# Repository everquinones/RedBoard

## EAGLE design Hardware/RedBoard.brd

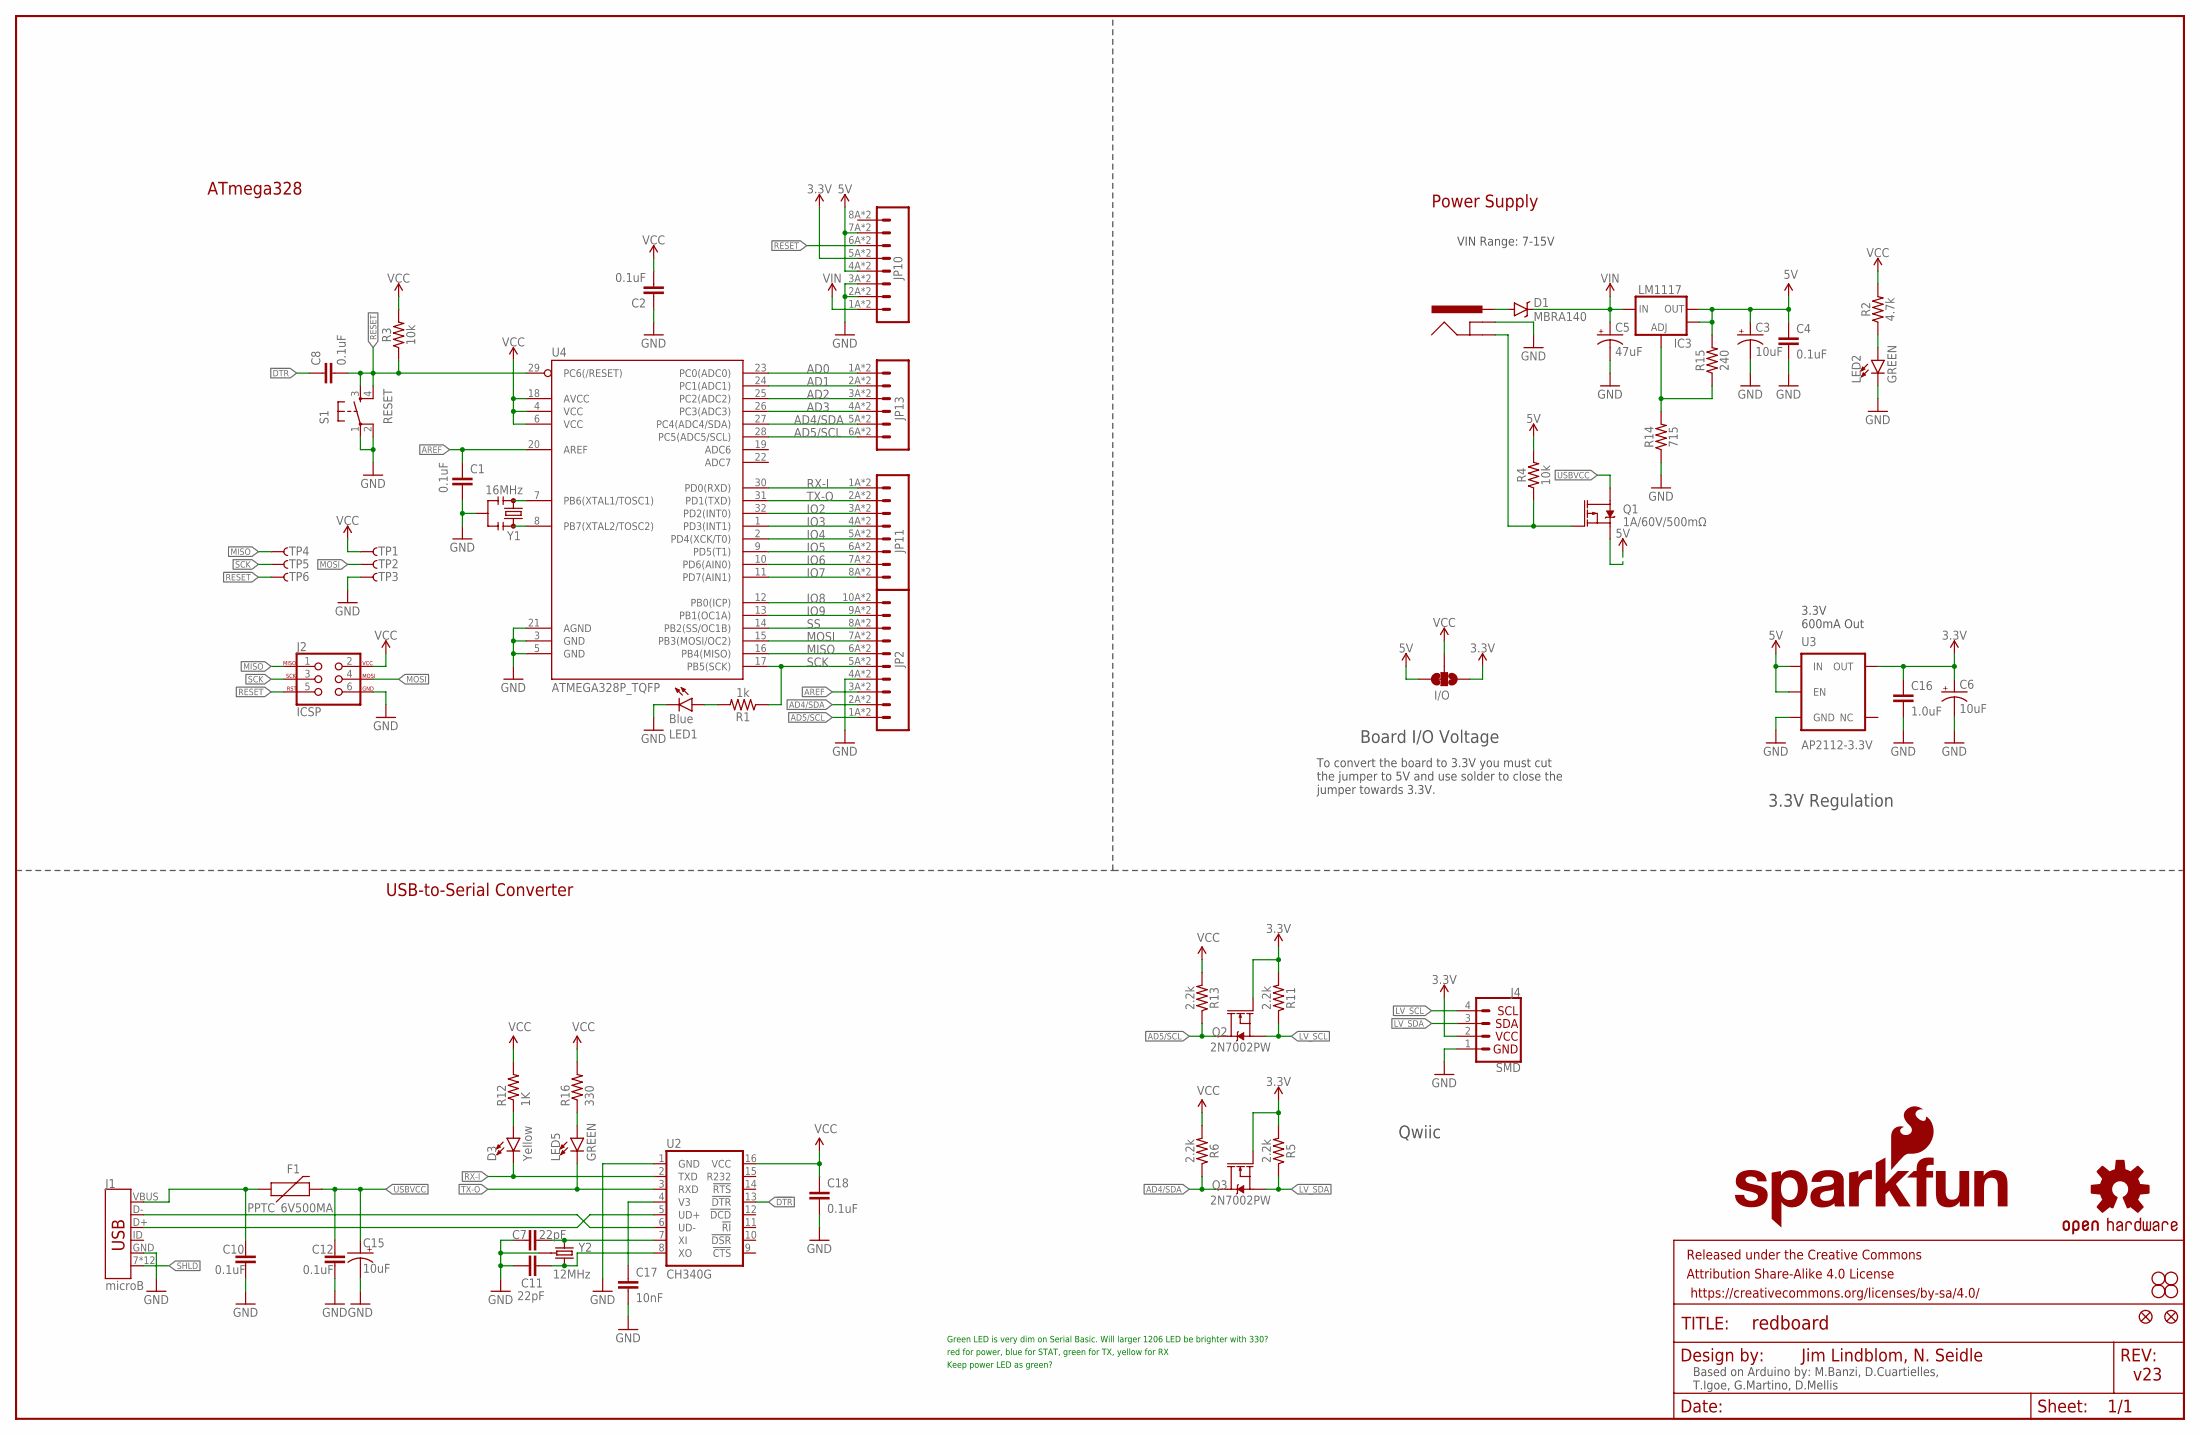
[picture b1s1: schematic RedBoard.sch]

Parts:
C1, C2, C4, C8, C10, C12: 0.1uF; 0603
C3, C6, C15: 10uF; EIA3216
C5: 47uF; PANASONIC_D
C7, C11: 22pF; 0603
C16: 1.0uF; 0603-CAP
C17: 10nF; 0603-CAP
C18: 0.1uF; 0603-CAP
D1: MBRA140; SMA-DIODE
D3: Yellow; LED-1206-HIDDENSILK
F1: PPTC_6V500MA; 0805
FRAME1: FRAME-LEDGER; CREATIVE_COMMONS
I/O: JUMPER-SMT_3_1-NC_TRACE_SILK; SMT-JUMPER_3_1-NC_TRACE_SILK
IC3: LM1117; SOT223-ALT1
J1: microB; USB-MICROB-PTH
J2: ICSP; 2X3_SMT_POSTS
J3: POWER_JACKSUPER_BOMB_DIGITY; POWER_JACK_SMD_OVERPASTE_SUPER_BOMB_DIGITY
J4: SMD; 1X04_1MM_RA
JP1: SFE_LOGO_NAME.1_INCH; SFE_LOGO_NAME_.1
JP2: M10SMD_COMBO; 1X10_SMD_COMBINED
JP3, JP4, JP5, JP6: STAND-OFF
JP7: SFE_LOGO_FLAME.1_INCH; SFE_LOGO_FLAME_.1
JP8, JP9: FIDUCIAL1X2; FIDUCIAL-1X2
JP10: M08SMD-COMBO; 1X08_SMD_COMBINED
JP11: JP11; 1X08_SMD_COMBINED
JP13: M06SMD-STRAIGHT-COMBO; 1X06_SMD_STRAIGHT_COMBO
LED1: Blue; LED-1206-HIDDENSILK
LED2, LED5: GREEN; LED-1206-HIDDENSILK
Q1: 1A/60V/500mΩ; SOT23-3
Q2, Q3: 2N7002PW; SOT323
R1: 1k; 0603
R2: 4.7k; 0603
R3, R4: 10k; 0603
R5, R6, R11, R13: 2.2k; 0603
R12: 1K; 0603-RES
R14: 715; 0603
R15: 240; 0603
R16: 330; 0603-RES
S1: RESET; TACTILE-SWITCH-SMD
TP1, TP2, TP3, TP4, TP5, TP6: TP-3x5; PAD.03X.05
U2: CH340G; SO016
U3: AP2112-3.3V; SOT23-5
U4: ATMEGA328P_TQFP; TQFP32-08
U$16: OSHW-LOGOS; OSHW-LOGO-S
Y1: 16MHz; RESONATOR-SMD-3.2X1.3
Y2: 12MHz; CRYSTAL-SMD-3.2X2.5

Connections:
3.3V: C6.+, C16.1, I/O.1, J4.2 (VCC), JP10.5A (5), JP10.5B (5), Q2.1 (G), Q3.1 (G), R5.2, R11.2, U3.5 (OUT)
5V: C3.+, C4.1, I/O.3, IC3.2 (OUT), IC3.4 (OUT), JP10.4A (4), JP10.4B (4), JP10.7A (7), JP10.7B (7), Q1.2 (S), R4.2, R15.2, U3.1 (IN), U3.3 (EN)
!DTR: C8.1, U2.13 (!DTR)
AD0: JP13.1A (1), JP13.1B (1), U4.23 (PC0(ADC0))
AD1: JP13.2A (2), JP13.2B (2), U4.24 (PC1(ADC1))
AD2: JP13.3A (3), JP13.3B (3), U4.25 (PC2(ADC2))
AD3: JP13.4A (4), JP13.4B (4), U4.26 (PC3(ADC3))
AD4/SDA: JP2.2A (2), JP2.2B (2), JP13.5A (5), JP13.5B (5), Q3.3 (D), R6.1, U4.27 (PC4(ADC4/SDA))
AD5/SCL: JP2.1A (1), JP2.1B (1), JP13.6A (6), JP13.6B (6), Q2.3 (D), R13.1, U4.28 (PC5(ADC5/SCL))
AREF: C1.1, JP2.3A (3), JP2.3B (3), U4.20 (AREF)
GND: C1.2, C2.1, C3.-, C4.2, C5.-, C6.-, C7.1, C10.2, C11.1, C12.2, C15.-, C16.2, C17.2, C18.2, J1.GND, J2.6, J3.GND (GNDBREAK), J4.1 (GND), JP2.4A (4), JP2.4B (4), JP10.2A (2), JP10.2B (2), JP10.3A (3), JP10.3B (3), LED1.C, LED2.C, R14.1, S1.1, S1.2, TP3.P$1, U2.1 (GND), U3.2 (GND), U4.3 (GND), U4.5 (GND), U4.21 (AGND), Y1.2, Y2.2 (GND), Y2.4 (GND)
INSERT: J3.P$4 (GND), Q1.1 (G), R4.1
IO2: JP11.3A (3), JP11.3B (3), U4.32 (PD2(INT0))
IO3: JP11.4A (4), JP11.4B (4), U4.1 (PD3(INT1))
IO4: JP11.5A (5), JP11.5B (5), U4.2 (PD4(XCK/T0))
IO5: JP11.6A (6), JP11.6B (6), U4.9 (PD5(T1))
IO6: JP11.7A (7), JP11.7B (7), U4.10 (PD6(AIN0))
IO7: JP11.8A (8), JP11.8B (8), U4.11 (PD7(AIN1))
IO8: JP2.10A (10), JP2.10B (10), U4.12 (PB0(ICP))
IO9: JP2.9A (9), JP2.9B (9), U4.13 (PB1(OC1A))
LV_SCL: J4.4 (SCL), Q2.2 (S), R11.1
LV_SDA: J4.3 (SDA), Q3.2 (S), R5.1
MISO: J2.1, JP2.6A (6), JP2.6B (6), TP4.P$1, U4.16 (PB4(MISO))
MOSI: J2.4, JP2.7A (7), JP2.7B (7), TP2.P$1, U4.15 (PB3(MOSI/OC2))
unnamed: LED1.A, R1.2
unnamed: LED2.A, R2.1
unnamed: U4.7 (PB6(XTAL1/TOSC1)), Y1.1
unnamed: U4.8 (PB7(XTAL2/TOSC2)), Y1.3
unnamed: LED5.A, R16.1
unnamed: D3.A, R12.1
unnamed: C11.2, U2.8 (XO), Y2.3 (2)
unnamed: C7.2, U2.7 (XI), Y2.1
unnamed: J1.D-, U2.6 (UD-)
unnamed: J1.D+, U2.5 (UD+)
unnamed: IC3.1 (ADJ), R14.2, R15.1
PWRIN: D1.A, J3.VIN0 (PWR)
RESET: C8.2, J2.5, JP10.6A (6), JP10.6B (6), R3.1, S1.3, S1.4, TP6.P$1, U4.29 (PC6(/RESET))
RX-I: D3.C, JP11.1A (1), JP11.1B (1), U2.2 (TXD), U4.30 (PD0(RXD))
SCK: J2.3, JP2.5A (5), JP2.5B (5), R1.1, TP5.P$1, U4.17 (PB5(SCK))
SHLD: J1.7 (SHIELD), J1.SHEILD2 (SHIELD), J1.SHIELD, J1.SHIELD3 (SHIELD), J1.SHIELD4 (SHIELD), J1.SHIELD5 (SHIELD), J1.SHIELD6 (SHIELD), J1.SHIELD8 (SHIELD), J1.SHIELD9 (SHIELD), J1.SHIELD10 (SHIELD), J1.SHIELD11 (SHIELD), J1.SHIELD12 (SHIELD)
SS: JP2.8A (8), JP2.8B (8), U4.14 (PB2(SS/OC1B))
TX-O: JP11.2A (2), JP11.2B (2), LED5.C, U2.3 (RXD), U4.31 (PD1(TXD))
USBVCC: C12.1, C15.+, F1.2, Q1.3 (D)
V3: C17.1, U2.4 (V3)
VCC: C2.2, C18.1, I/O.2, J2.2, R2.2, R3.2, R6.2, R12.2, R13.2, R16.2, TP1.P$1, U2.16 (VCC), U4.4 (VCC), U4.6 (VCC), U4.18 (AVCC)
VIN: C5.+, D1.C, IC3.3 (IN), JP10.1A (1), JP10.1B (1)
VUSB: C10.1, F1.1, J1.VBUS

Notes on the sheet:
Power Supply
ATmega328
USB-to-Serial Converter
Based on Arduino by: M.Banzi, D.Cuartielles, T.Igoe, G.Martino, D.Mellis
Jim Lindblom, N. Seidle
v23
VIN Range: 7-15V
3.3V Regulation
3.3V 600mA Out
Green LED is very dim on Serial Basic. Will larger 1206 LED be brighter with 330?
Board I/O Voltage
To convert the board to 3.3V you must cut the jumper to 5V and use solder to close the jumper towards 3.3V.
Qwiic
red for power, blue for STAT, green for TX, yellow for RX
Keep power LED as green?

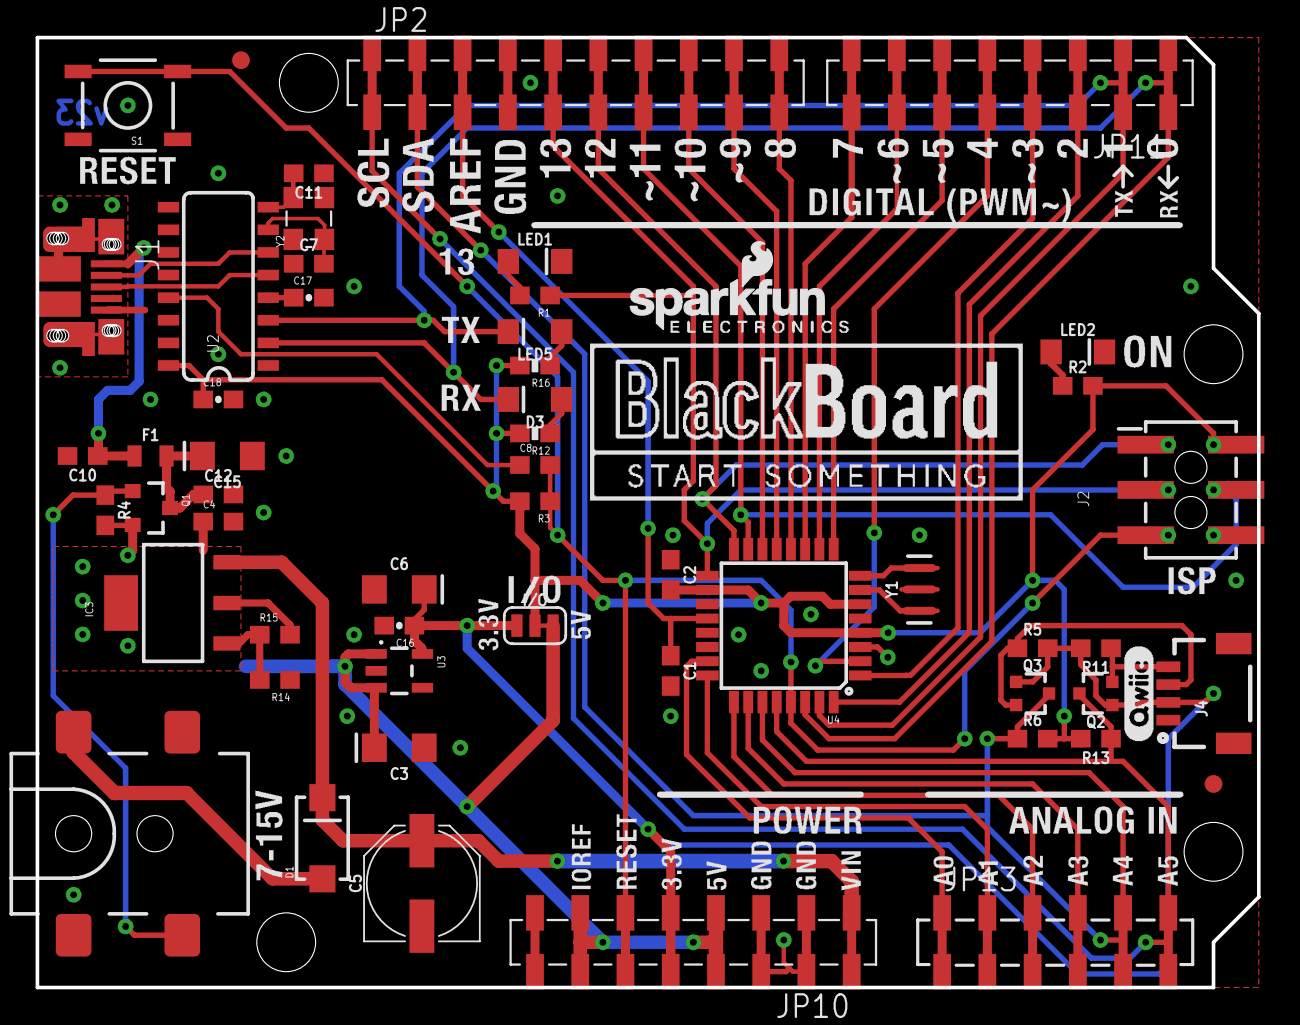
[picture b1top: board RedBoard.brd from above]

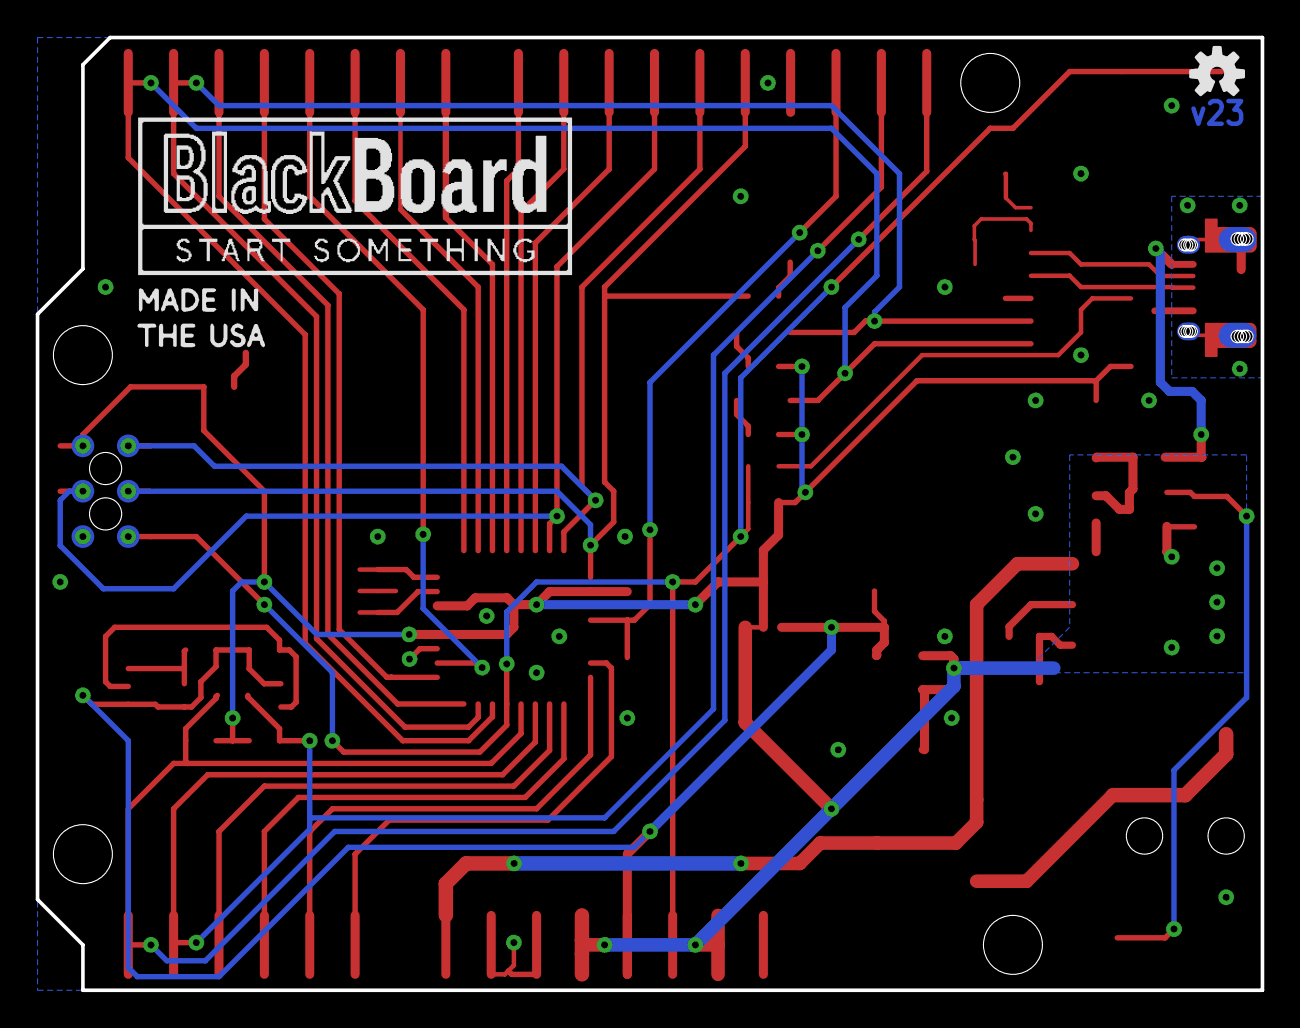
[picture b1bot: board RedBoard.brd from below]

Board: 2 copper layers, 68.6 x 53.3 mm, 72 parts (9 on the bottom side), 47 nets.

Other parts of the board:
U$1, U$3: BLACKBOARDLOGO#PNG
U$2: (QWIIC)
U$4: MADEINUSA#PNG

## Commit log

2018-03-28 Initial commit.
    Changed USB. Added Qwiic. Added I/O jumper.
2018-04-04 Rolling version on PCB
2018-04-04 Silk Changes
    "BlackBoard / Made In The USA" Silk Added

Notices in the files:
parts and their libraries:
SparkFun-Aesthetics: Licensing: CC v3.0 Share-Alike You are welcome to use this library for commercial purposes.
SparkFun-Aesthetics: Released under the Creative Commons Attribution Share-Alike 4.0 License
SparkFun-Aesthetics: https://creativecommons.org/licenses/by-sa/4.0
